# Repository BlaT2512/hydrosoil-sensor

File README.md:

# HydroSensor

This repository is part of HydroSoil, and contains the latest firmware and some revisions of CAD designs for HydroSensor and HydroSensor Pro. 

HydroSensor's are ultra-low-power devices, running custom embedded firmware designed to communicate with the HydroSoil network.

HydroSensor's are engineered for high-reliability, minimal loss of data, and long battery life. The firmware features:

- Simple cryptographic hashing of REST payloads for API security & replay protection, using built-in RF physical noise registers (`ESP.random()`)
- Tracking of internal battery and soil moisture level, as well as ambient light, temperature and humidity for Pro sensor
- Non-volatile data backups to local disk with tracking of timestamps. During times of unstable network connection, HydroSensor's seemlessly continue readings locally and upload all stored readings when connection is restored, ensuring that virtually no data is lost
- Usage of internal RTC RAM cache to store a running clock in relation to failed network requests, to bypass the lack of a physical RTC, and avoid network/battery overhead of communicating with NTP servers. A CRC32 checksum algorithm is also use d to validate integrity of the RAM on boot cycles
- Dynamic sleep times to intelligently conserve power, calculated based off of environment change delta reading-over-reading, readings compared to normal thresholds, and number of failed requests if server is unreachable
- A "dumb edge, smart cloud" pattern is used in the ecosystem in order to offload processing of data to the HydroSoil cloud, including calculation of dynamic sleep time and conversion of raw sensor readings to usable data.
- RTC RAM cache is used for time data as it is frequently written to in order to preserve silicon wear (limit of about 100,000 writes), and filesystem storage is used for data backup as it is more persistent, and writes are much less frequent - only on network failure

## Tech Stack
The microcontroller the firmware runs on is an Espressif ESP-12F chip, a single-core RISC architecture. The chip is run at 80MHz to preserve battery.
The microcontroller is wired to:
- 1x ADS1115 (a 16-bit ADC over I2C chip, used for readings from the soil moisture sensor)
- 1x SHT-31D (I2C digital temperature and humidity sensor)
- 1x TSL2591 (I2C digital visible & infrared light sensor)

The firmware is written in C++ and utilises PlatformIO core and Espressif 8266 development package. The firmware also uses LittleFS for communication with filesystem storage, WiFiManager for emitting a captive portal when WiFi is not configured, and standard Adafruit libraries for each peripheral used listed above.

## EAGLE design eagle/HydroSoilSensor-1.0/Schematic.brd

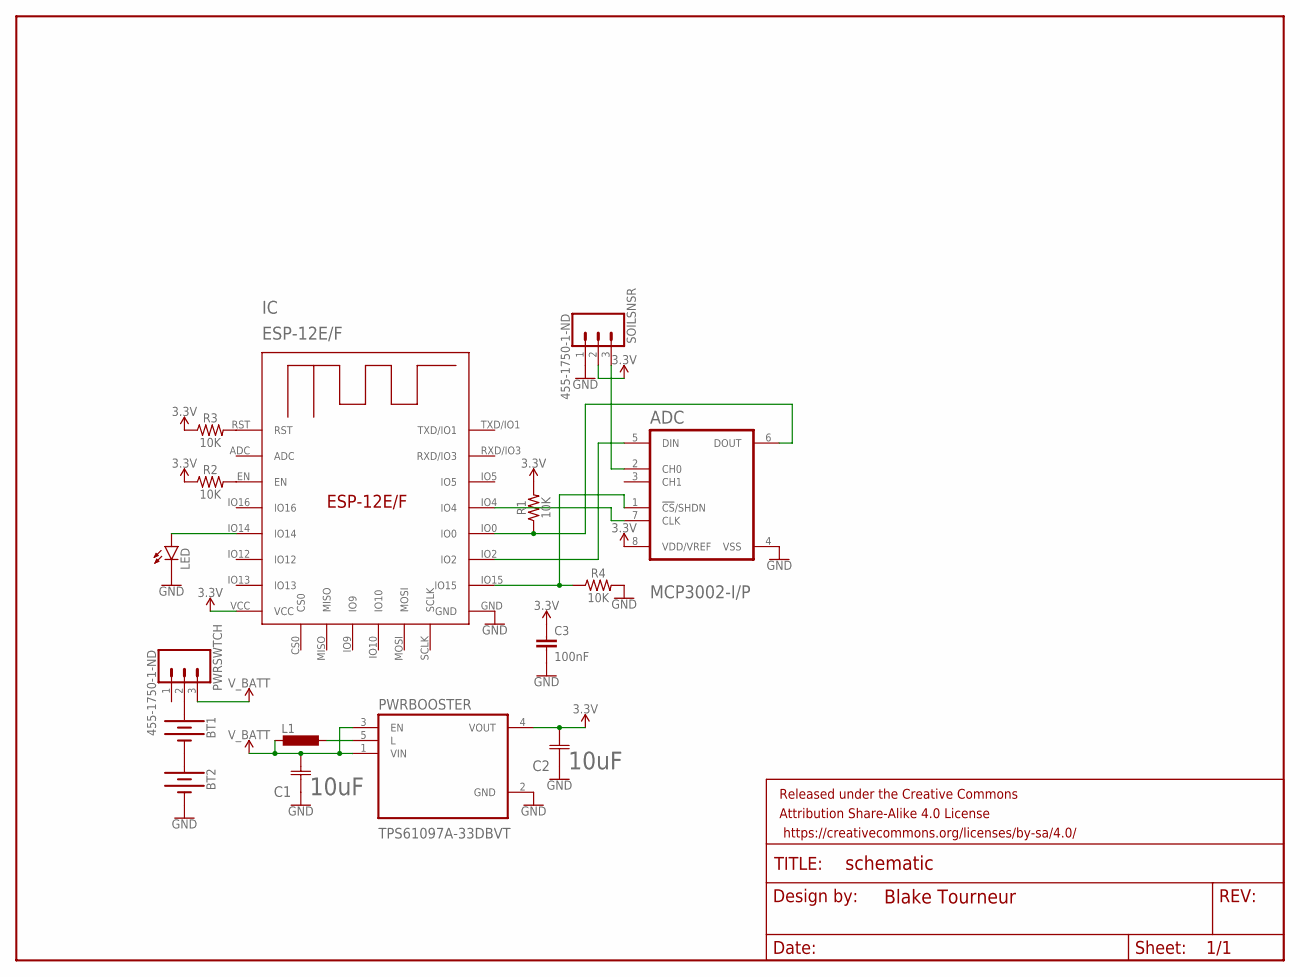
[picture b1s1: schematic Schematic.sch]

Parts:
ADC: MICROCHIP_MCP3002-I-PMICROCHIP_MCP3002-I-P_0_0; MICROCHIP_MCP3002-I-P_0
BT1, BT2: BATTERY-AA
C1, C2: 10uF; CAPC3216X180N
C3: 100nF; C2.5-3
FRAME1: FRAME-LETTERNO_PACKAGE; DUMMY
IC: ESP-12E/F; ESP-12E
L1: DO3316P
LED: LED3MM
PWRBOOSTER: TPS61097A-33DBVT; SOT95P280X145-5N
PWRSWTCH: 455-1750-1-ND; 1X03
R1, R2, R3, R4: 10K; 0402-TIGHT
SOILSNSR: 455-1750-1-ND; 1X03

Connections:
3.3V: ADC.8 (VDD/VREF), C2.2 (C2), C3.1, IC.VCC, PWRBOOSTER.4 (VOUT), R1.2, R2.1, R3.1, SOILSNSR.2
ASENS0: ADC.2 (CH0), SOILSNSR.3
COIL: L1.2, PWRBOOSTER.5 (L)
CS: ADC.1 (!CS!/SHDN), IC.IO15, R4.1
GND: ADC.4 (VSS), BT2.GND@1 (-), C1.1 (C1), C2.1 (C1), C3.2, IC.GND, LED.K (C), PWRBOOSTER.2 (GND), R4.2, SOILSNSR.1
IO0: ADC.6 (DOUT), IC.IO0, R1.1
LED: IC.IO14, LED.A
MCPCLK: ADC.7 (CLK), IC.IO4
MCPDIN: ADC.5 (DIN), IC.IO2
unnamed: BT1.GND@1 (-), BT2.PWR@1 (+)
unnamed: BT1.PWR@1 (+), PWRSWTCH.2
unnamed: IC.EN, R2.2
unnamed: IC.RST, R3.2
V_BATT: C1.2 (C2), L1.1, PWRBOOSTER.1 (VIN), PWRBOOSTER.3 (EN), PWRSWTCH.3

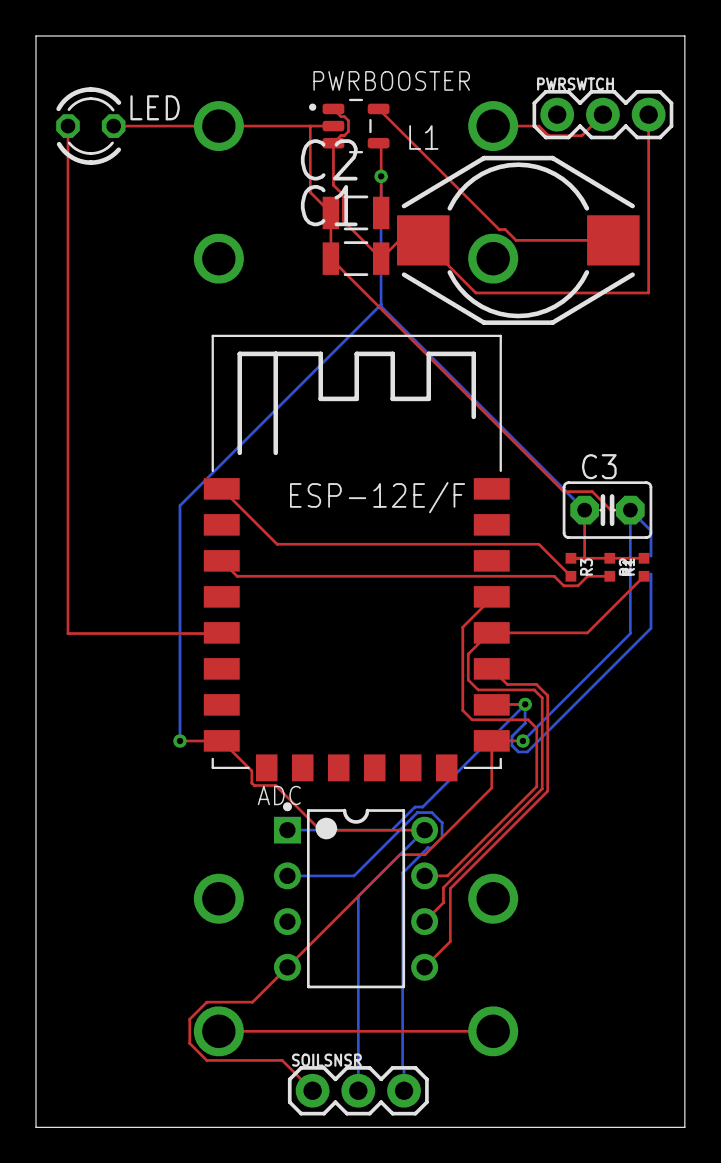
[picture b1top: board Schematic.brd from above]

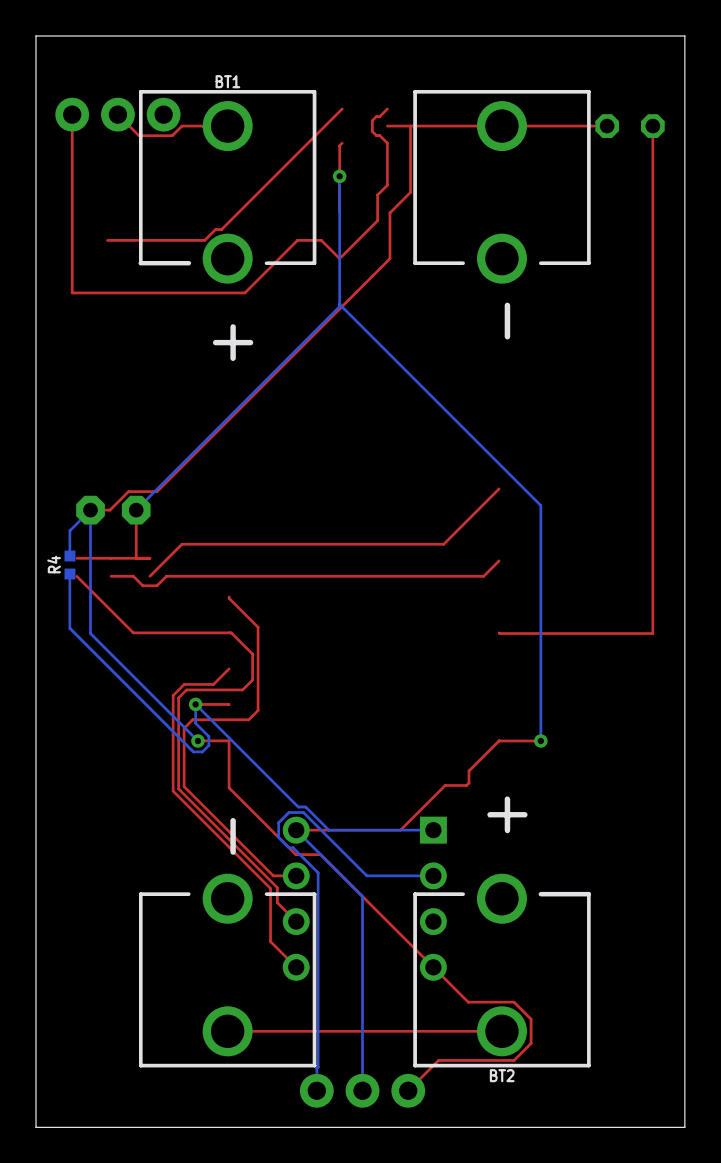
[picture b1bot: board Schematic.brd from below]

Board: 2 copper layers, 36.0 x 60.6 mm, 17 parts (3 on the bottom side), 14 nets.

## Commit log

2026-05-27 Add HydroSensor 2.0, 2.1 firmware, 1.0 CAD
    Can't find CAD for version 2.0 board utilising the newer decided hardware in firmware 2.x

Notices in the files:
parts and their libraries:
SparkFun-Batteries: Licensing: Creative Commons ShareAlike 4.0 International - https://creativecommons.org/licenses/by-sa/4.0
SparkFun-Aesthetics: Released under the Creative Commons Attribution Share-Alike 4.0 License
SparkFun-Aesthetics: https://creativecommons.org/licenses/by-sa/4.0
